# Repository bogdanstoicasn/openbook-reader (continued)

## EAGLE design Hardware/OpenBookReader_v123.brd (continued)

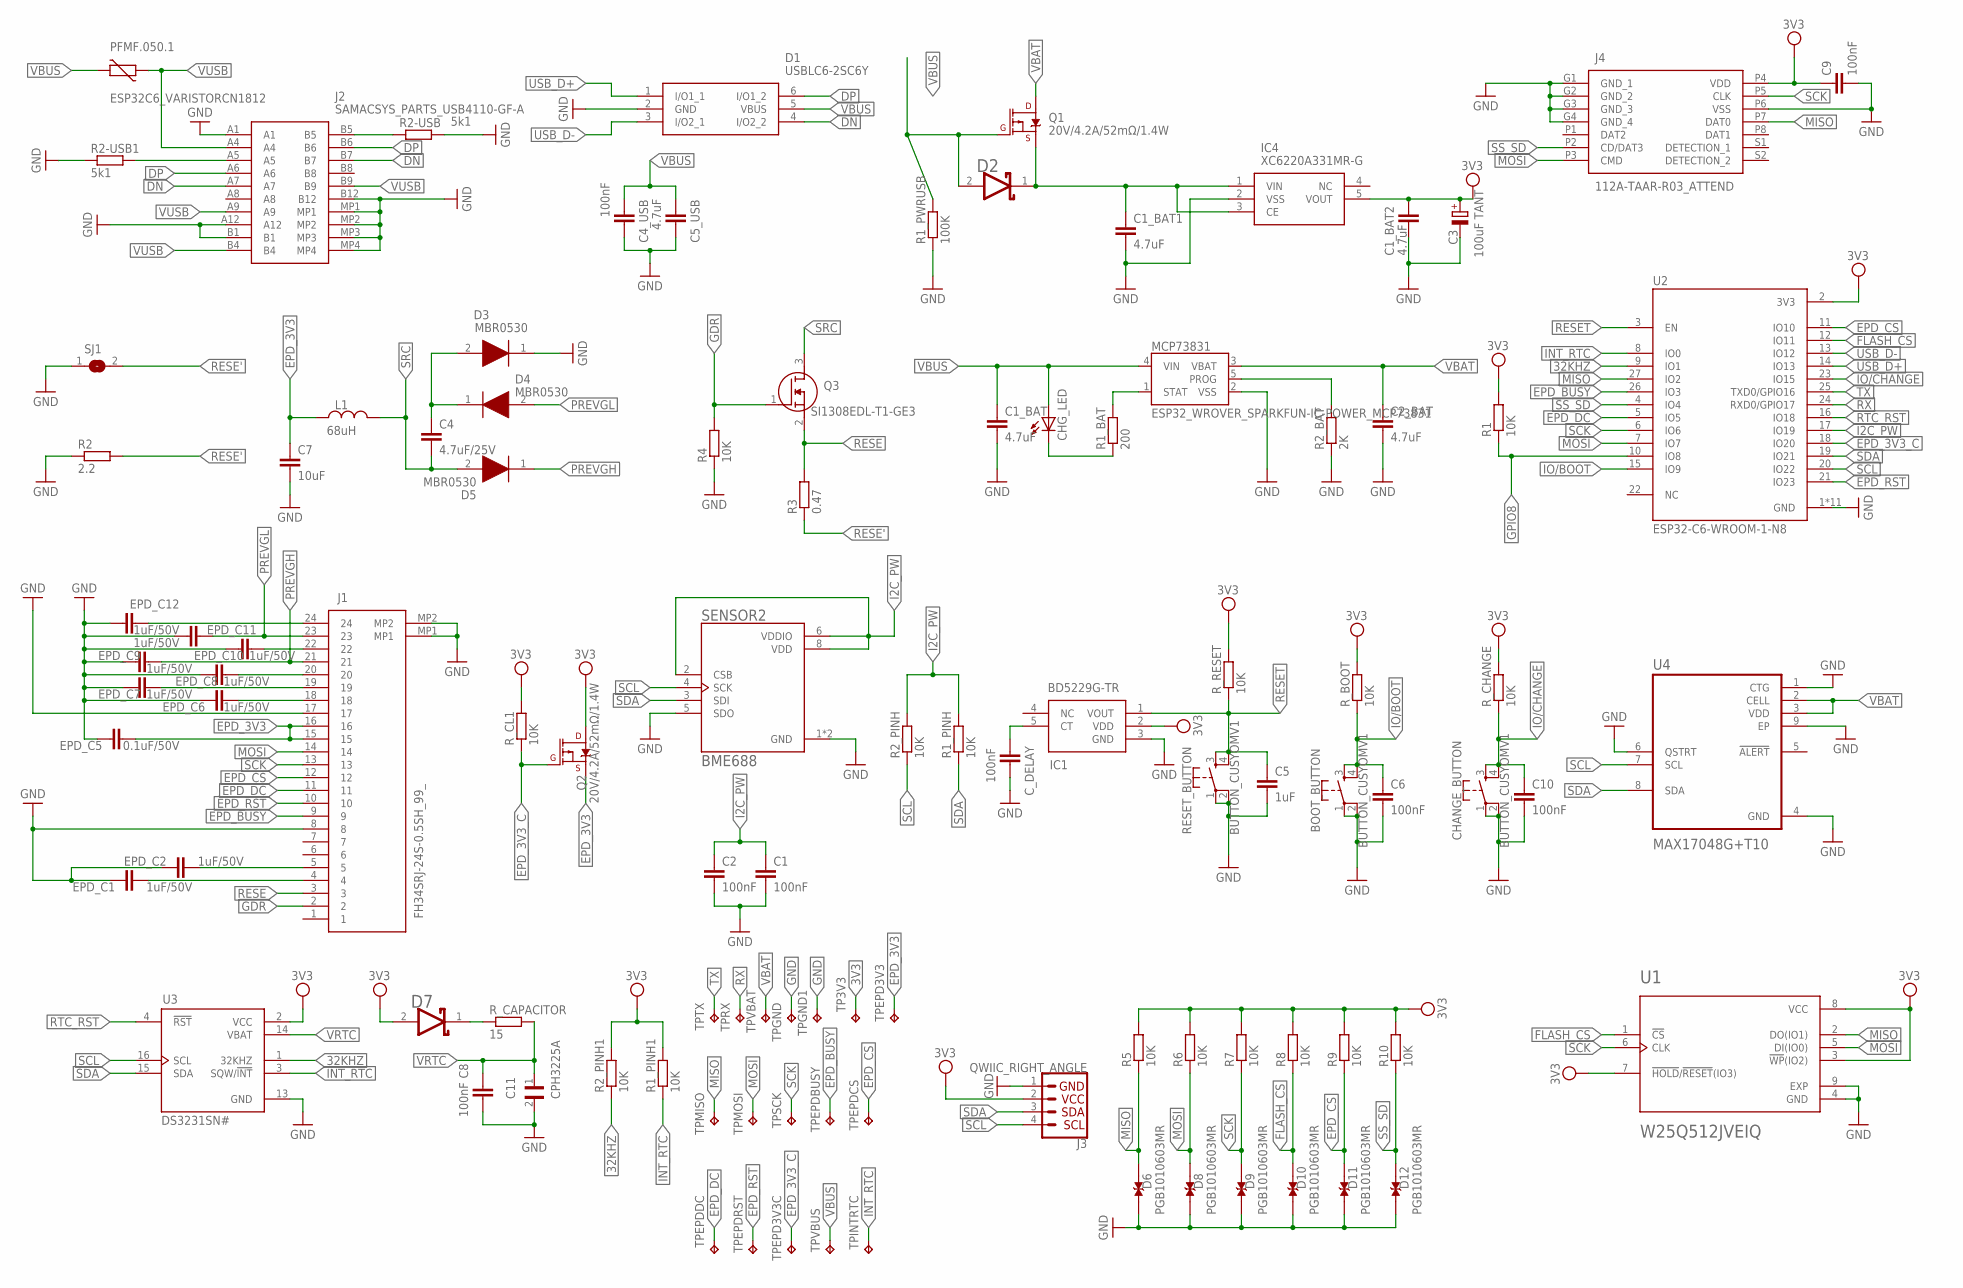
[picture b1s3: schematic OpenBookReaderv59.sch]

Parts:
BOOT_BUTTON: BUTTON_CUSYOMV1; MYBUTTON
C1, C2, C4_USB, C6, C8, C9, C10: 100nF; EAGLE-LTSPICE_C0402
C1_BAT, C1_BAT1, C1_BAT2, C2_BAT, C5_USB: 4.7uF; EAGLE-LTSPICE_C0402
C3: 100uF TANT; RCL_CT3528
C4: 4.7uF/25V; EAGLE-LTSPICE_C0402
C5: 1uF; EAGLE-LTSPICE_C0402
C7: 10uF; EAGLE-LTSPICE_C0402
C11: CPH3225A; CAPCP3225X100N
CHANGE_BUTTON: BUTTON_CUSYOMV1; MYBUTTON
CHG_LED: ADAFRUIT_LEDCHIP-LED0603; ADAFRUIT_CHIP-LED0603
C_DELAY: 100nF; EAGLE-LTSPICE_C0402
D1: USBLC6-2SC6Y; SOT95P280X145-6N
D2, D7: ESP32_WROVER_AVX---SD0805S020S1R0_AVX_SD0805S020S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; ESP32_WROVER_AVX---SD0805S020S1R0_AVX_SD0805S020S1R0_0
D3, D4, D5: MBR0530; SOD3716X135N
D6, D8, D9, D10, D11, D12: PGB1010603MR; DIOC1608X36N
EPD_C1, EPD_C2, EPD_C6, EPD_C7, EPD_C8, EPD_C9, EPD_C10, EPD_C11, EPD_C12: 1uF/50V; EAGLE-LTSPICE_C0402
EPD_C5: 0.1uF/50V; EAGLE-LTSPICE_C0402
IC1: BD5229G-TR; SOT95P280X125-5N
IC4: XC6220A331MR-G; SOT95P280X120-5N
J1: FH34SRJ-24S-0.5SH_99_; FH34SRJ24S05SH99
J2: SAMACSYS_PARTS_USB4110-GF-A; SAMACSYS_PARTS_USB4110GFA
J3: QWIIC_RIGHT_ANGLE; JST04_1MM_RA
J4: 112A-TAAR-R03_ATTEND; 112ATAARR03ATTEND
L1: 68uH; INDC1006X60N
MCP73831: ESP32_WROVER_SPARKFUN-IC-POWER_MCP73831; ESP32_WROVER_SPARKFUN-IC-POWER_SOT23-5
PFMF.050.1: ESP32C6_VARISTORCN1812; ESP32C6_VARISTOR_CT/CN1812
Q1, Q2: 20V/4.2A/52mΩ/1.4W; ESP32_WROVER_SPARKFUN-DISCRETESEMI_SOT23-3
Q3: SI1308EDL-T1-GE3; SOT65P210X110-3N
R1, R1_PINH, R1_PINH1, R2_PINH, R2_PINH1, R4, R5, R6, R7, R8, R9, R10: 10K; ESP32_WROVER_EAGLE-LTSPICE_R0402
R1_BAT: 200; ESP32_WROVER_EAGLE-LTSPICE_R0402
R1_PWRUSB: 100K; ESP32_WROVER_EAGLE-LTSPICE_R0402
R2: 2.2; ESP32_WROVER_EAGLE-LTSPICE_R0402
R2-USB, R2-USB1: 5k1; ESP32_WROVER_EAGLE-LTSPICE_R0402
R2_BAT: 2K; ESP32_WROVER_EAGLE-LTSPICE_R0402
R3: 0.47; ESP32_WROVER_EAGLE-LTSPICE_R0402
RESET_BUTTON: BUTTON_CUSYOMV1; MYBUTTON
R_BOOT: 10K; ESP32_WROVER_EAGLE-LTSPICE_R0402
R_CAPACITOR: 15; ESP32_WROVER_EAGLE-LTSPICE_R0402
R_CHANGE: 10K; ESP32_WROVER_EAGLE-LTSPICE_R0402
R_CL1: 10K; ESP32_WROVER_EAGLE-LTSPICE_R0402
R_RESET: 10K; ESP32_WROVER_EAGLE-LTSPICE_R0402
SENSOR2: BME688; ESP32_WROVER_BME680_PSON80P300X300X100-8N
SJ1: SJ
TP3V3: TPTP20R; TP20R
TPEPD3V3, TPEPD3V3C: TPTP20R; TP20R
TPEPDBUSY: TPTP20R; TP20R
TPEPDCS: TPTP20R; TP20R
TPEPDDC: TPTP20R; TP20R
TPEPDRST: TPTP20R; TP20R
TPGND, TPGND1: TPTP20R; TP20R
TPINTRTC: TPTP20R; TP20R
TPMISO: TPTP20R; TP20R
TPMOSI: TPTP20R; TP20R
TPRX: TPTP20R; TP20R
TPSCK: TPTP20R; TP20R
TPTX: TPTP20R; TP20R
TPVBAT: TPTP20R; TP20R
TPVBUS: TPTP20R; TP20R
U1: W25Q512JVEIQ; SON127P600X800X80-9N
U2: ESP32-C6-WROOM-1-N8; XCVR_ESP32-C6-WROOM-1-N8
U3: DS3231SN#; SOIC127P1032X265-16N
U4: MAX17048G+T10; SON50P200X200X80-9N

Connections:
3V3: C1_BAT2.1, C3.+, C9.1, D7.2 (ANODE), IC1.2 (VDD), IC4.5 (VOUT), J3.2, J4.P4 (VDD), Q2.3 (D), R1.2, R1_PINH1.2, R2_PINH1.2, R5.2, R6.2, R7.2, R8.2, R9.2, R10.2, R_BOOT.2, R_CHANGE.2, R_CL1.2, R_RESET.2, TP3V3.TP, U1.3 (!WP!(IO2)), U1.7 (!HOLD!/!RESET!(IO3)), U1.8 (VCC), U2.2 (3V3), U3.2 (VCC)
32KHZ: R2_PINH1.1, U2.9 (IO1), U3.1 (32KHZ)
DN: D1.4 (I/O2_2), J2.A7, J2.B7
DP: D1.6 (I/O1_2), J2.A6, J2.B6
EPD_3V3: C7.1, EPD_C5.2, J1.15, J1.16, L1.1, Q2.2 (S), TPEPD3V3.TP
EPD_3V3_C: Q2.1 (G), R_CL1.1, TPEPD3V3C.TP, U2.18 (IO20)
EPD_BUSY: J1.9, TPEPDBUSY.TP, U2.26 (IO3)
EPD_CS: D11.2, J1.12, R9.1, TPEPDCS.TP, U2.11 (IO10)
EPD_DC: J1.11, TPEPDDC.TP, U2.5 (IO5)
EPD_RST: J1.10, TPEPDRST.TP, U2.21 (IO23)
FLASH_CS: D10.2, R8.1, U1.1 (!CS), U2.12 (IO11)
GDR: J1.2, Q3.1 (G), R4.2
GND: BOOT_BUTTON.1, BOOT_BUTTON.2, C1.2, C1_BAT.2, C1_BAT1.2, C1_BAT2.2, C2.2, C2_BAT.2, C3.-, C4_USB.2, C5.2, C5_USB.2, C6.2, C7.2, C8.2, C9.2, C10.2, C11.2, CHANGE_BUTTON.1, CHANGE_BUTTON.2, C_DELAY.2, D1.2 (GND), D3.1 (K), D6.1, D8.1, D9.1, D10.1, D11.1, D12.1, EPD_C1.1, EPD_C2.1, EPD_C5.1, EPD_C6.1, EPD_C7.1, EPD_C8.1, EPD_C9.1, EPD_C10.1, EPD_C11.1, EPD_C12.1, IC1.3 (GND), IC4.2 (VSS), J1.8, J1.17, J1.MP1, J1.MP2, J2.A1, J2.A12, J2.B1, J2.B12, J2.MP1, J2.MP2, J2.MP3, J2.MP4, J3.1, J4.G1 (GND_1), J4.G2 (GND_2), J4.G3 (GND_3), J4.G4 (GND_4), J4.P6 (VSS), MCP73831.2 (VSS), R1_PWRUSB.1, R2.1, R2-USB.2, R2-USB1.1, R2_BAT.1, R4.1, RESET_BUTTON.1, RESET_BUTTON.2, SENSOR2.1 (GND), SENSOR2.5 (SDO), SENSOR2.7 (GND), SJ1.1, TPGND.TP, TPGND1.TP, U1.4 (GND), U1.9 (EXP), U2.1 (GND), U2.28 (GND), U2.29_1 (GND), U2.29_2 (GND), U2.29_3 (GND), U2.29_4 (GND), U2.29_5 (GND), U2.29_6 (GND), U2.29_7 (GND), U2.29_8 (GND), U2.29_9 (GND), U3.13 (GND), U4.1 (CTG), U4.4 (GND), U4.6 (QSTRT), U4.9 (EP)
GPIO8: R1.1, U2.10 (IO8)
I2C_PW: C1.1, C2.1, R1_PINH.2, R2_PINH.2, SENSOR2.2 (CSB), SENSOR2.6 (VDDIO), SENSOR2.8 (VDD), U2.17 (IO19)
INT_RTC: R1_PINH1.1, TPINTRTC.TP, U2.8 (IO0), U3.3 (SQW/!INT)
IO/BOOT: BOOT_BUTTON.3, BOOT_BUTTON.4, C6.1, R_BOOT.1, U2.15 (IO9)
IO/CHANGE: C10.1, CHANGE_BUTTON.3, CHANGE_BUTTON.4, R_CHANGE.1, U2.23 (IO15)
MISO: D6.2, J4.P7 (DAT0), R5.1, TPMISO.TP, U1.2 (DO(IO1)), U2.27 (IO2)
MOSI: D8.2, J1.14, J4.P3 (CMD), R6.1, TPMOSI.TP, U1.5 (DI(IO0)), U2.7 (IO7)
unnamed: J2.A5, R2-USB1.2
unnamed: J2.B5, R2-USB.1
unnamed: C1_BAT1.1, D2.1 (CATHODE), IC4.1 (VIN), IC4.3 (CE), Q1.2 (S)
unnamed: MCP73831.1 (STAT), R1_BAT.2
unnamed: C4.1, D3.2 (A), D4.1 (K)
unnamed: CHG_LED.C, R1_BAT.1
unnamed: MCP73831.5 (PROG), R2_BAT.2
unnamed: EPD_C12.2, J1.24
unnamed: EPD_C10.2, J1.22
unnamed: EPD_C8.2, J1.20
unnamed: EPD_C7.2, J1.19
unnamed: EPD_C6.2, J1.18
unnamed: EPD_C2.2, J1.5
unnamed: EPD_C1.2, J1.4
unnamed: C_DELAY.1, IC1.5 (CT)
unnamed: D7.1 (CATHODE), R_CAPACITOR.1
PREVGH: D5.1 (K), EPD_C9.2, J1.21
PREVGL: D4.2 (A), EPD_C11.2, J1.23
RESE: J1.3, Q3.2 (S), R3.2
RESE': R2.2, R3.1, SJ1.2
RESET: C5.1, IC1.1 (VOUT), RESET_BUTTON.3, RESET_BUTTON.4, R_RESET.1, U2.3 (EN)
RTC_RST: U2.16 (IO18), U3.4 (!RST)
RX: TPRX.TP, U2.24 (RXD0/GPIO17)
SCK: D9.2, J1.13, J4.P5 (CLK), R7.1, TPSCK.TP, U1.6 (CLK), U2.6 (IO6)
SCL: J3.4, R2_PINH.1, SENSOR2.4 (SCK), U2.20 (IO22), U3.16 (SCL), U4.7 (SCL)
SDA: J3.3, R1_PINH.1, SENSOR2.3 (SDI), U2.19 (IO21), U3.15 (SDA), U4.8 (SDA)
SRC: C4.2, D5.2 (A), L1.2, Q3.3 (D)
SS_SD: D12.2, J4.P2 (CD/DAT3), R10.1, U2.4 (IO4)
TX: TPTX.TP, U2.25 (TXD0/GPIO16)
USB_D+: D1.1 (I/O1_1), U2.14 (IO13)
USB_D-: D1.3 (I/O2_1), U2.13 (IO12)
VBAT: C2_BAT.1, MCP73831.3 (VBAT), Q1.3 (D), TPVBAT.TP, U4.2 (CELL), U4.3 (VDD)
VBUS: C1_BAT.1, C4_USB.1, C5_USB.1, CHG_LED.A, D1.5 (VBUS), D2.2 (ANODE), MCP73831.4 (VIN), PFMF.050.1.2, Q1.1 (G), R1_PWRUSB.2, TPVBUS.TP
VRTC: C8.1, C11.1, R_CAPACITOR.2, U3.14 (VBAT)
VUSB: J2.A4, J2.A9, J2.B4, J2.B9, PFMF.050.1.1

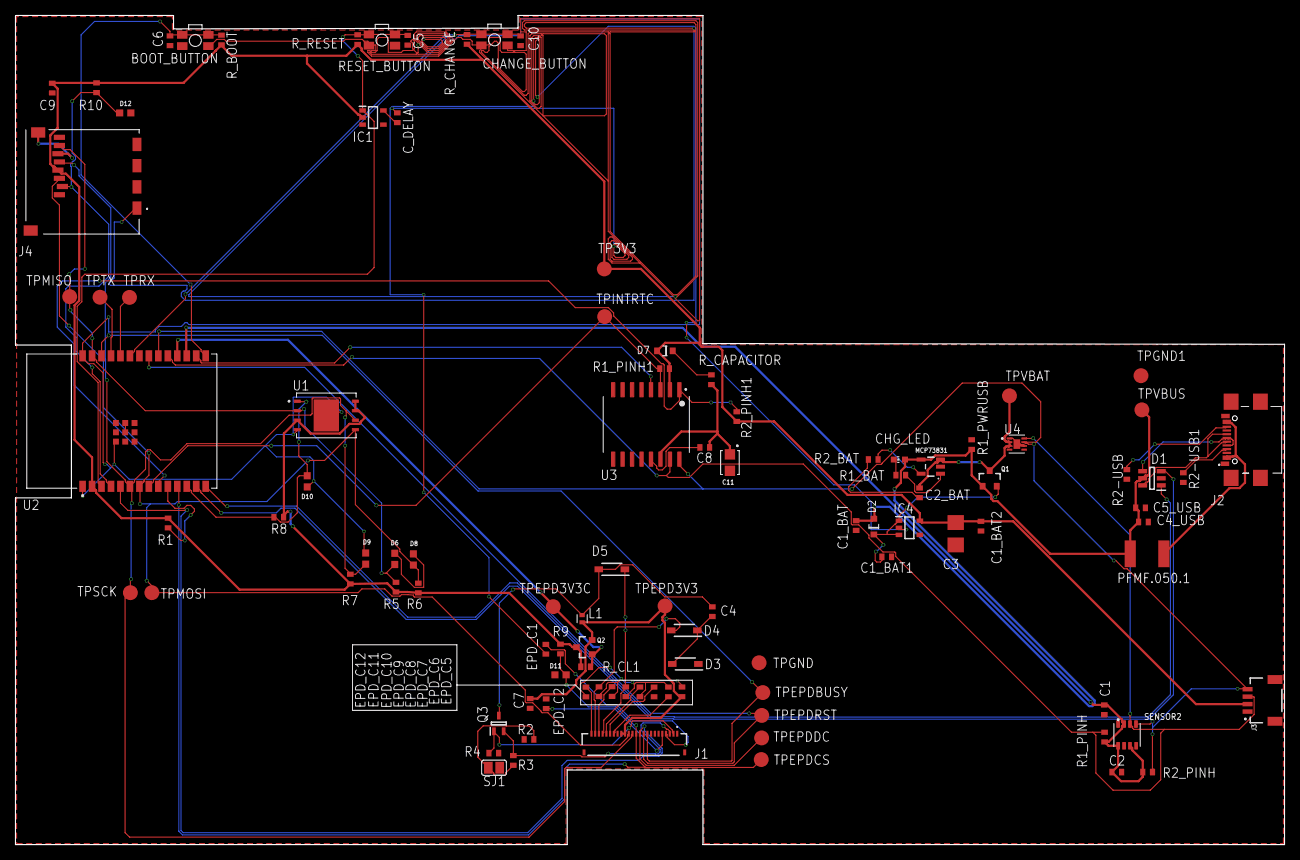
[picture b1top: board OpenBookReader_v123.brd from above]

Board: 2 copper layers, 170.2 x 111.2 mm, 103 parts (0 on the bottom side), 55 nets.

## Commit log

2025-03-30 Create LICENSE
2025-03-31 Pick and place+BOM+Gerbers
2025-03-31 Mechanical.zip upload
    Contains an expldoed view model and the fully assembled model
2025-03-31 Rendering
2025-04-02 Renew sd card
2025-04-02 Update datasheets and hardware
2025-04-02 working on the readme
2025-04-02 Block Diagram
